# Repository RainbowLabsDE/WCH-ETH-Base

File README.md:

# WCH-ETH-Base
A WCH ETH Board for a Case

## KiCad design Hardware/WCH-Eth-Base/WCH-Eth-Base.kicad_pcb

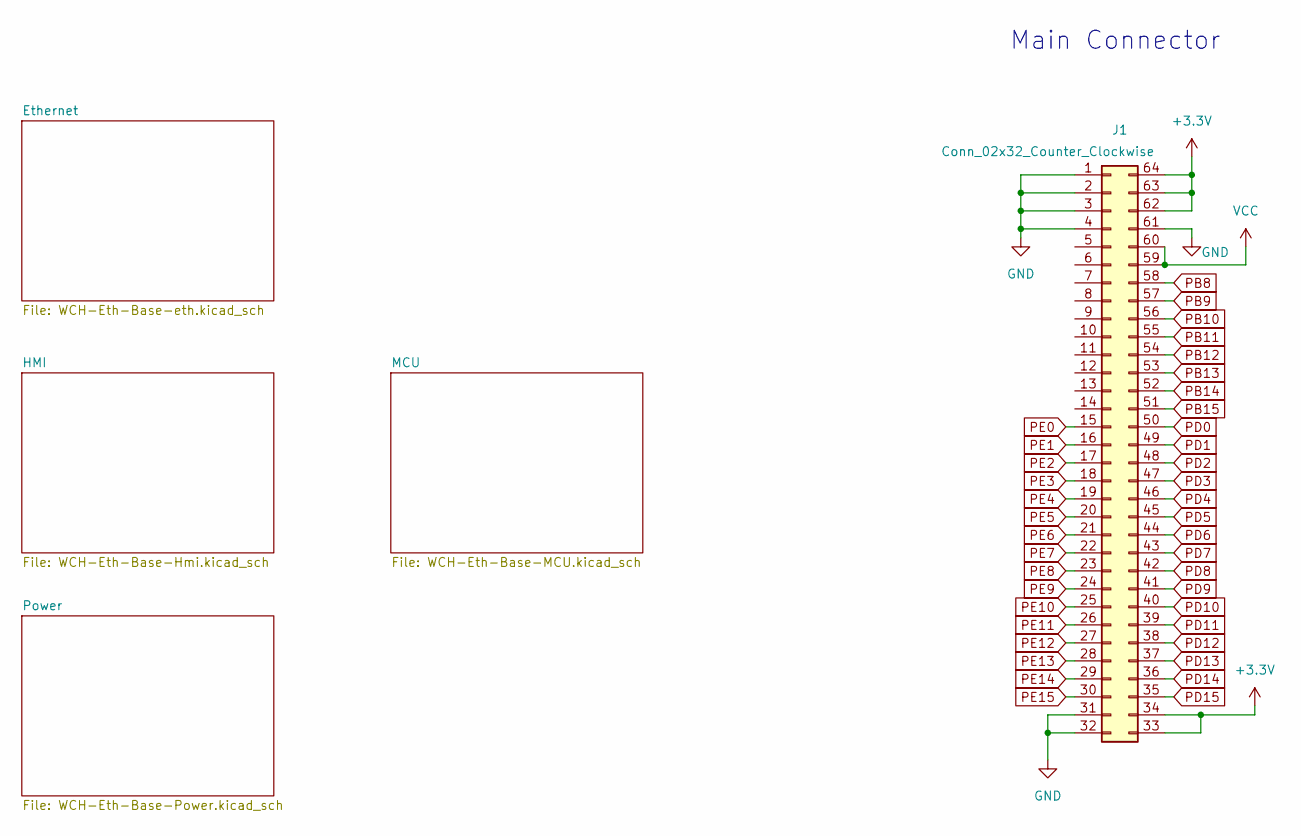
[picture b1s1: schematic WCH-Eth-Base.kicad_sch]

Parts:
J1: Conn_02x32_Counter_Clockwise; CONN-SMD_64P_3157-10101D

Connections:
+3.3V: J1.33, J1.34, J1.62, J1.63, J1.64; also elsewhere on the board
GND: J1.1, J1.2, J1.3, J1.4, J1.31, J1.32, J1.61; also elsewhere on the board
PB8: J1.58; also elsewhere on the board
PB9: J1.57; also elsewhere on the board
PB10: J1.56; also elsewhere on the board
PB11: J1.55; also elsewhere on the board
PB12: J1.54; also elsewhere on the board
PB13: J1.53; also elsewhere on the board
PB14: J1.52; also elsewhere on the board
PB15: J1.51; also elsewhere on the board
PD0: J1.50; also elsewhere on the board
PD1: J1.49; also elsewhere on the board
PD2: J1.48; also elsewhere on the board
PD3: J1.47; also elsewhere on the board
PD4: J1.46; also elsewhere on the board
PD5: J1.45; also elsewhere on the board
PD6: J1.44; also elsewhere on the board
PD7: J1.43; also elsewhere on the board
PD8: J1.42; also elsewhere on the board
PD9: J1.41; also elsewhere on the board
PD10: J1.40; also elsewhere on the board
PD11: J1.39; also elsewhere on the board
PD12: J1.38; also elsewhere on the board
PD13: J1.37; also elsewhere on the board
PD14: J1.36; also elsewhere on the board
PD15: J1.35; also elsewhere on the board
PE0: J1.15; also elsewhere on the board
PE1: J1.16; also elsewhere on the board
PE2: J1.17; also elsewhere on the board
PE3: J1.18; also elsewhere on the board
PE4: J1.19; also elsewhere on the board
PE5: J1.20; also elsewhere on the board
PE6: J1.21; also elsewhere on the board
PE7: J1.22; also elsewhere on the board
PE8: J1.23; also elsewhere on the board
PE9: J1.24; also elsewhere on the board
PE10: J1.25; also elsewhere on the board
PE11: J1.26; also elsewhere on the board
PE12: J1.27; also elsewhere on the board
PE13: J1.28; also elsewhere on the board
PE14: J1.29; also elsewhere on the board
PE15: J1.30; also elsewhere on the board
VCC: J1.59, J1.60; also elsewhere on the board

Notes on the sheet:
Main Connector

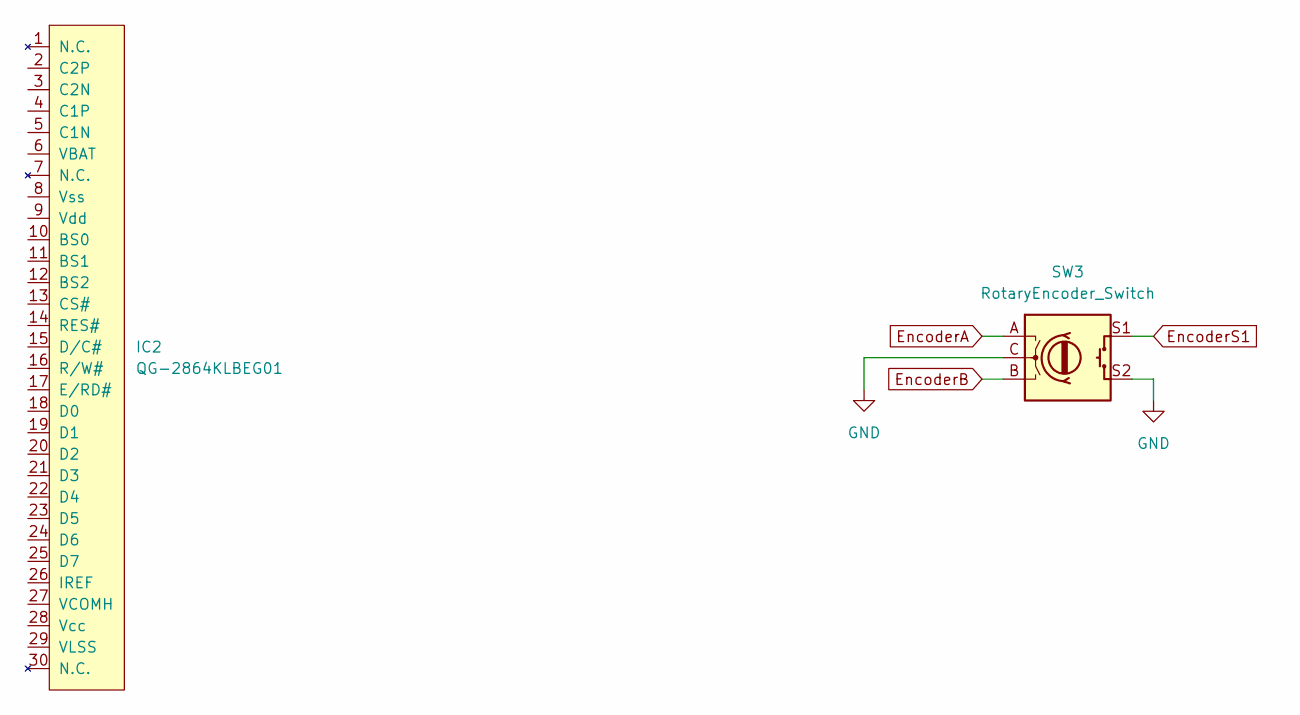
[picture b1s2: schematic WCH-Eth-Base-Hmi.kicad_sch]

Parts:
IC2: QG-2864KLBEG01
SW3: RotaryEncoder_Switch; STEC11B09

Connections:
EncoderA: SW3.A
EncoderB: SW3.B
EncoderS1: SW3.S1
GND: SW3.C, SW3.S2; also elsewhere on the board

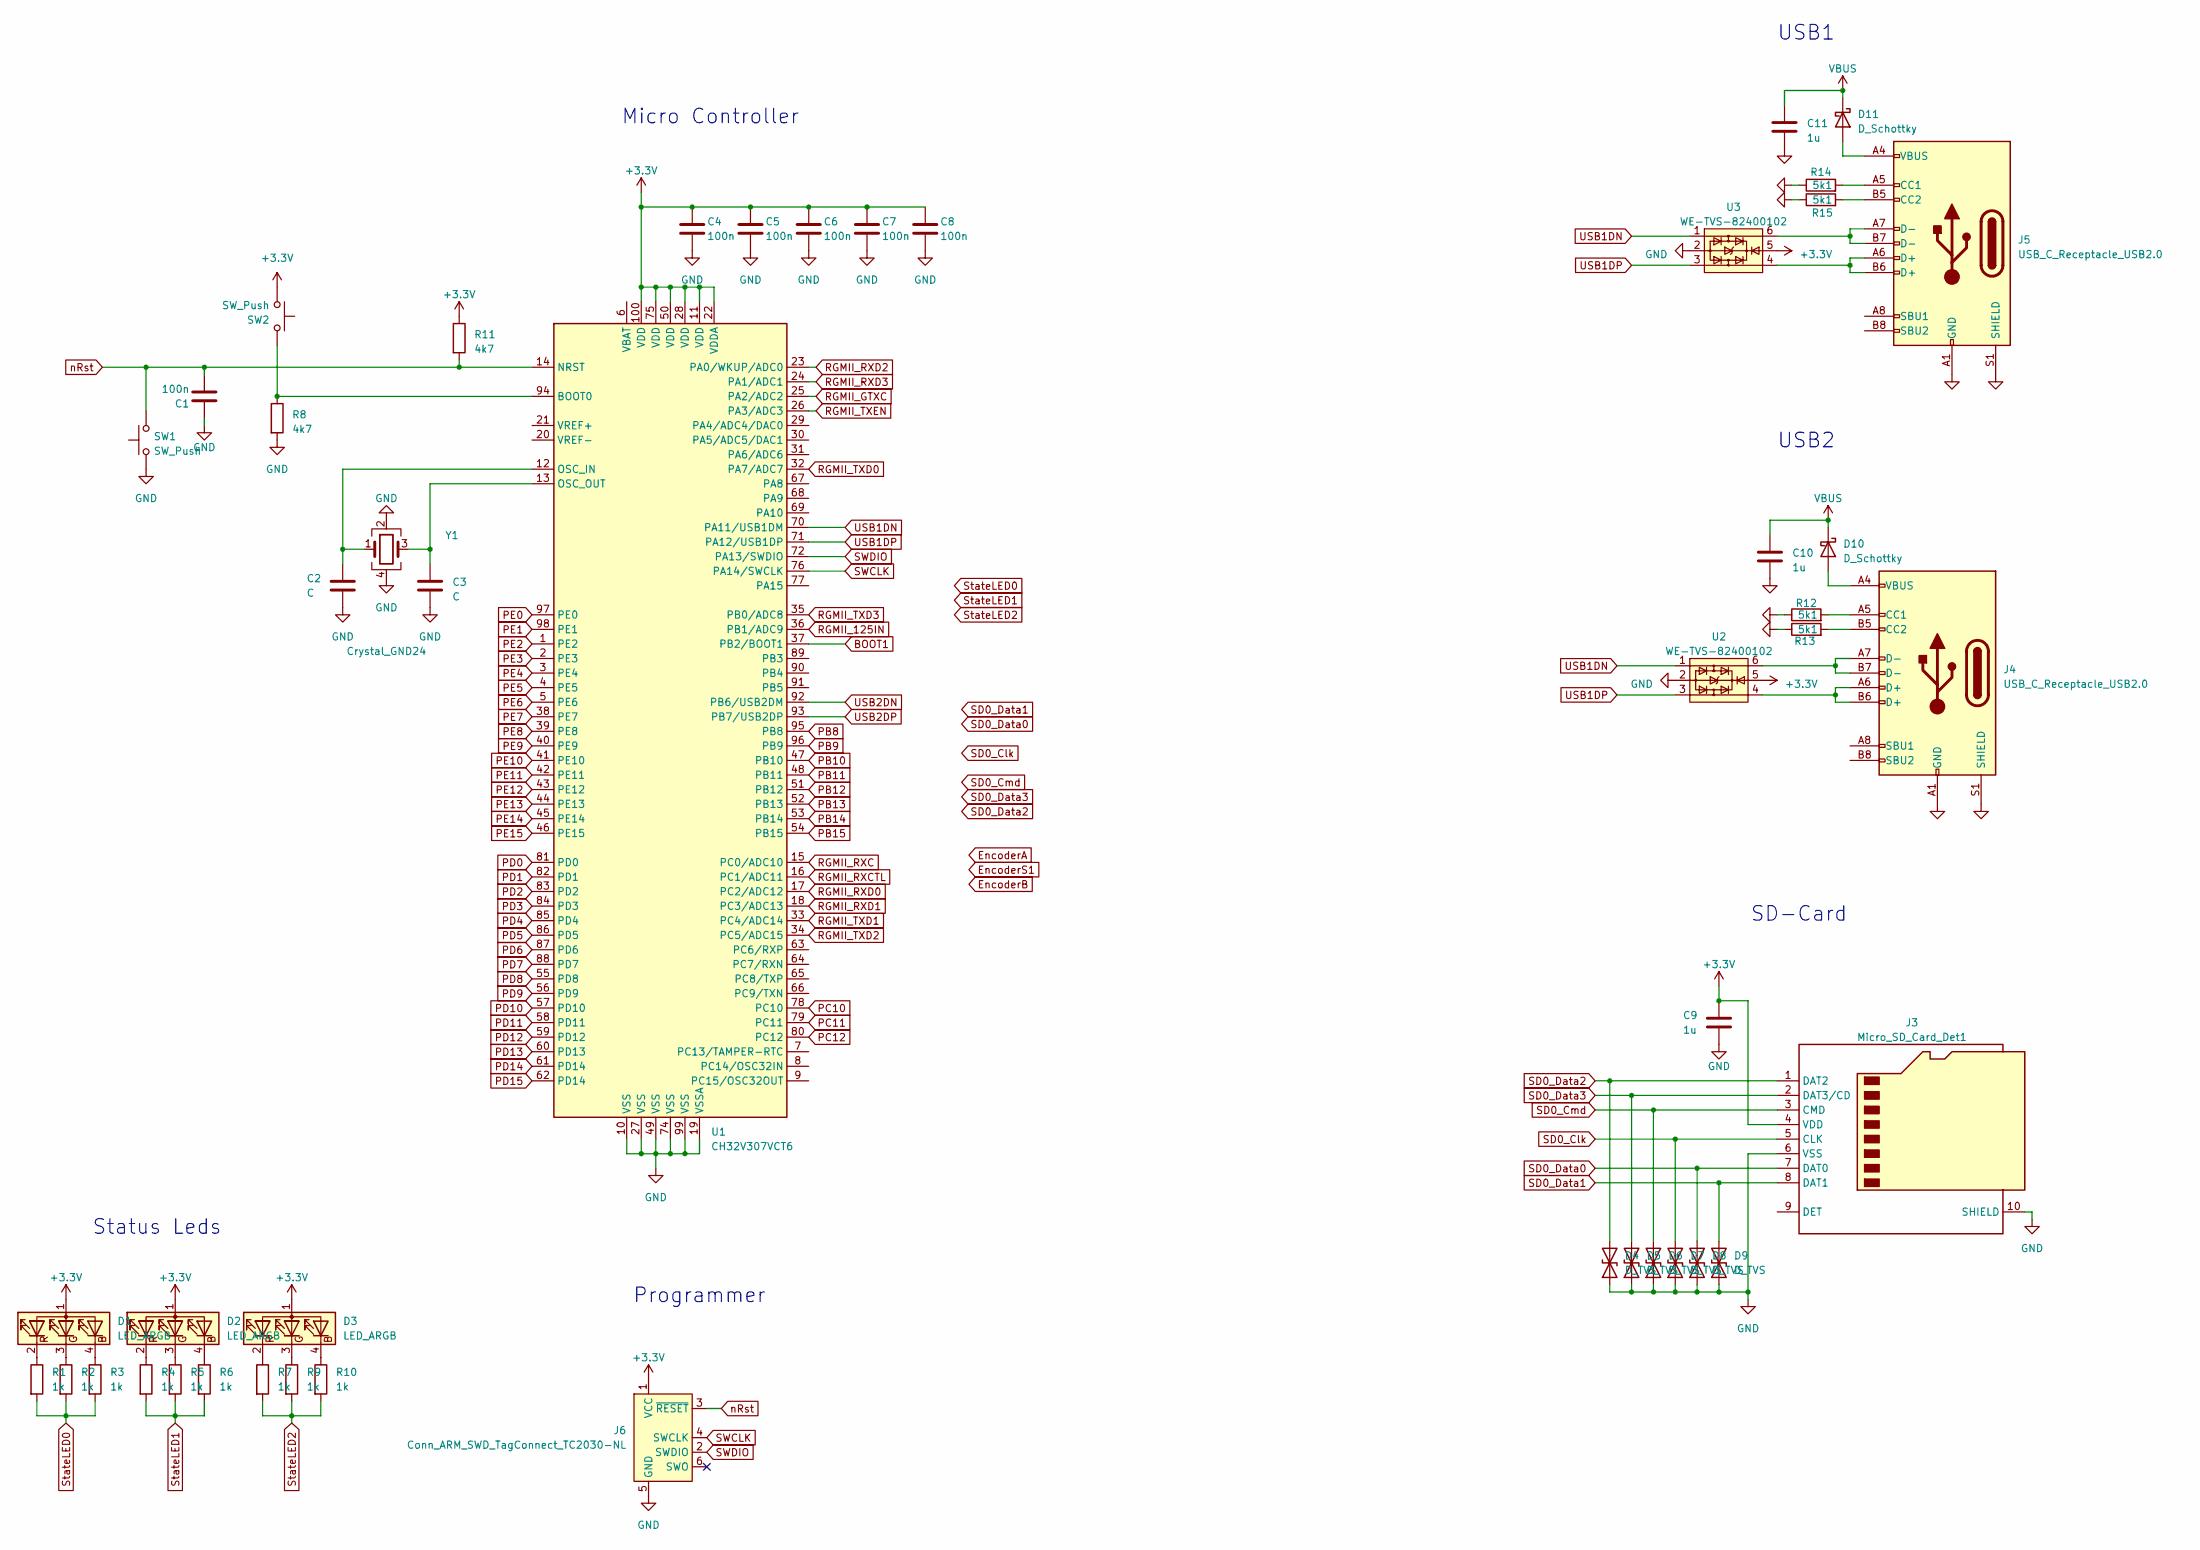
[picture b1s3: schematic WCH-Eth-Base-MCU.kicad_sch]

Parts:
C1, C4, C5, C6, C7, C8: 100n; C_0402_1005Metric
C2, C3: C; C_0402_1005Metric
C9, C10, C11: 1u; C_0402_1005Metric
D1, D2, D3: LED_ARGB; LED-ARRAY-SMD_MHS110FRGBCT
D4: D_TVS; D_SMA
D5, D6, D7, D8, D9: D_TVS
D10, D11: D_Schottky; D_SMA
J3: Micro_SD_Card_Det1
J4, J5: USB_C_Receptacle_USB2.0; TYPE-C-TH_TYPE-C-14P-CC-2.6
J6: Conn_ARM_SWD_TagConnect_TC2030-NL; Tag-Connect_TC2030-IDC-NL_2x03_P1.27mm_Vertical
R1, R2, R3, R4, R5, R6, R7, R9, R10: 1k; R_0402_1005Metric
R8, R11: 4k7; R_0402_1005Metric
R12, R13, R14, R15: 5k1; R_0402_1005Metric
SW1, SW2: SW_Push; SW-SMD_4P-L5.1-W5.1-P3.70-LS6.5-TL-2
U1: CH32V307VCT6; LQFP-100_14x14mm_P0.5mm
U2, U3: WE-TVS-82400102; SOT-23-6
Y1: Crystal_GND24; Crystal_SMD_3225-4Pin_3.2x2.5mm

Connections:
+3.3V: C4.1, C5.1, C6.1, C7.1, C8.1, C9.1, D1.1 (A), D2.1 (A), D3.1 (A), J3.4 (VDD), J6.1 (VCC), R11.1, SW2.1, U1.11 (VDD), U1.22 (VDDA), U1.28 (VDD), U1.50 (VDD), U1.75 (VDD), U1.100 (VDD), U2.5, U3.5; also elsewhere on the board
BOOT1: U1.37 (PB2/BOOT1)
GND: C1.1, C2.2, C3.2, C4.2, C5.2, C6.2, C7.2, C8.2, C9.2, C10.2, C11.2, D4.1 (A1), D5.1 (A1), D6.1 (A1), D7.1 (A1), D8.1 (A1), D9.1 (A1), J3.6 (VSS), J3.10 (SHIELD), J4.A1 (GND), J4.A12 (GND), J4.B1 (GND), J4.B12 (GND), J4.S1 (SHIELD), J5.A1 (GND), J5.A12 (GND), J5.B1 (GND), J5.B12 (GND), J5.S1 (SHIELD), J6.5 (GND), R8.2, R12.1, R13.1, R14.1, R15.1, SW1.1, U1.10 (VSS), U1.19 (VSSA), U1.27 (VSS), U1.49 (VSS), U1.74 (VSS), U1.99 (VSS), U2.2, U3.2, Y1.2, Y1.4; also elsewhere on the board
unnamed: D1.4 (BK), R3.1
unnamed: D1.3 (GK), R2.1
unnamed: D1.2 (RK), R1.1
unnamed: D2.4 (BK), R6.1
unnamed: D2.3 (GK), R5.1
unnamed: D2.2 (RK), R4.1
unnamed: D3.4 (BK), R10.1
unnamed: D3.3 (GK), R9.1
unnamed: D3.2 (RK), R7.1
unnamed: D5.2 (A2), J3.2 (DAT3/CD)
unnamed: D6.2 (A2), J3.3 (CMD)
unnamed: D7.2 (A2), J3.5 (CLK)
unnamed: D8.2 (A2), J3.7 (DAT0)
unnamed: D9.2 (A2), J3.8 (DAT1)
unnamed: D10.2 (A), J4.A4 (VBUS), J4.A9 (VBUS), J4.B4 (VBUS), J4.B9 (VBUS)
unnamed: D11.2 (A), J5.A4 (VBUS), J5.A9 (VBUS), J5.B4 (VBUS), J5.B9 (VBUS)
unnamed: J4.A5 (CC1), R12.2
unnamed: J4.B5 (CC2), R13.2
unnamed: J4.A6 (D+), J4.B6 (D+), U2.4
unnamed: J4.A7 (D-), J4.B7 (D-), U2.6
unnamed: J5.A5 (CC1), R14.2
unnamed: J5.B5 (CC2), R15.2
unnamed: J5.A6 (D+), J5.B6 (D+), U3.4
unnamed: J5.A7 (D-), J5.B7 (D-), U3.6
unnamed: R8.1, SW2.2, U1.94 (BOOT0)
unnamed: C2.1, U1.12 (OSC_IN), Y1.1
unnamed: C3.1, U1.13 (OSC_OUT), Y1.3
PB8: U1.95 (PB8); also elsewhere on the board
PB9: U1.96 (PB9); also elsewhere on the board
PB10: U1.47 (PB10); also elsewhere on the board
PB11: U1.48 (PB11); also elsewhere on the board
PB12: U1.51 (PB12); also elsewhere on the board
PB13: U1.52 (PB13); also elsewhere on the board
PB14: U1.53 (PB14); also elsewhere on the board
PB15: U1.54 (PB15); also elsewhere on the board
PC10: U1.78 (PC10)
PC11: U1.79 (PC11)
PC12: U1.80 (PC12)
PD0: U1.81 (PD0); also elsewhere on the board
PD1: U1.82 (PD1); also elsewhere on the board
PD2: U1.83 (PD2); also elsewhere on the board
PD3: U1.84 (PD3); also elsewhere on the board
PD4: U1.85 (PD4); also elsewhere on the board
PD5: U1.86 (PD5); also elsewhere on the board
PD6: U1.87 (PD6); also elsewhere on the board
PD7: U1.88 (PD7); also elsewhere on the board
PD8: U1.55 (PD8); also elsewhere on the board
PD9: U1.56 (PD9); also elsewhere on the board
PD10: U1.57 (PD10); also elsewhere on the board
PD11: U1.58 (PD11); also elsewhere on the board
PD12: U1.59 (PD12); also elsewhere on the board
PD13: U1.60 (PD13); also elsewhere on the board
PD14: U1.61 (PD14); also elsewhere on the board
PD15: U1.62 (PD14); also elsewhere on the board
PE0: U1.97 (PE0); also elsewhere on the board
PE1: U1.98 (PE1); also elsewhere on the board
PE2: U1.1 (PE2); also elsewhere on the board
PE3: U1.2 (PE3); also elsewhere on the board
PE4: U1.3 (PE4); also elsewhere on the board
PE5: U1.4 (PE5); also elsewhere on the board
PE6: U1.5 (PE6); also elsewhere on the board
PE7: U1.38 (PE7); also elsewhere on the board
PE8: U1.39 (PE8); also elsewhere on the board
PE9: U1.40 (PE9); also elsewhere on the board
PE10: U1.41 (PE10); also elsewhere on the board
PE11: U1.42 (PE11); also elsewhere on the board
PE12: U1.43 (PE12); also elsewhere on the board
PE13: U1.44 (PE13); also elsewhere on the board
PE14: U1.45 (PE14); also elsewhere on the board
PE15: U1.46 (PE15); also elsewhere on the board
RGMII_125IN: U1.36 (PB1/ADC9)
RGMII_GTXC: U1.25 (PA2/ADC2)
RGMII_RXC: U1.15 (PC0/ADC10)
RGMII_RXCTL: U1.16 (PC1/ADC11)
RGMII_RXD0: U1.17 (PC2/ADC12)
RGMII_RXD1: U1.18 (PC3/ADC13)
RGMII_RXD2: U1.23 (PA0/WKUP/ADC0)
RGMII_RXD3: U1.24 (PA1/ADC1)
RGMII_TXD0: U1.32 (PA7/ADC7)
RGMII_TXD1: U1.33 (PC4/ADC14)
RGMII_TXD2: U1.34 (PC5/ADC15)
RGMII_TXD3: U1.35 (PB0/ADC8)
RGMII_TXEN: U1.26 (PA3/ADC3)
SD0_Data2: D4.2 (A2), J3.1 (DAT2)
SWCLK: J6.4 (SWCLK), U1.76 (PA14/SWCLK)
SWDIO: J6.2 (SWDIO), U1.72 (PA13/SWDIO)
StateLED0: R1.2, R2.2, R3.2
StateLED1: R4.2, R5.2, R6.2
StateLED2: R7.2, R9.2, R10.2
USB1DN: U1.70 (PA11/USB1DM), U2.1, U3.1
USB1DP: U1.71 (PA12/USB1DP), U2.3, U3.3
USB2DN: U1.92 (PB6/USB2DM)
USB2DP: U1.93 (PB7/USB2DP)
VBUS: C10.1, C11.1, D10.1 (K), D11.1 (K); also elsewhere on the board
nRst: C1.2, J6.3 (~RESET), R11.2, SW1.2, U1.14 (NRST)

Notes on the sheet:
SD-Card
USB2
Programmer
USB1
Status Leds
Micro Controller

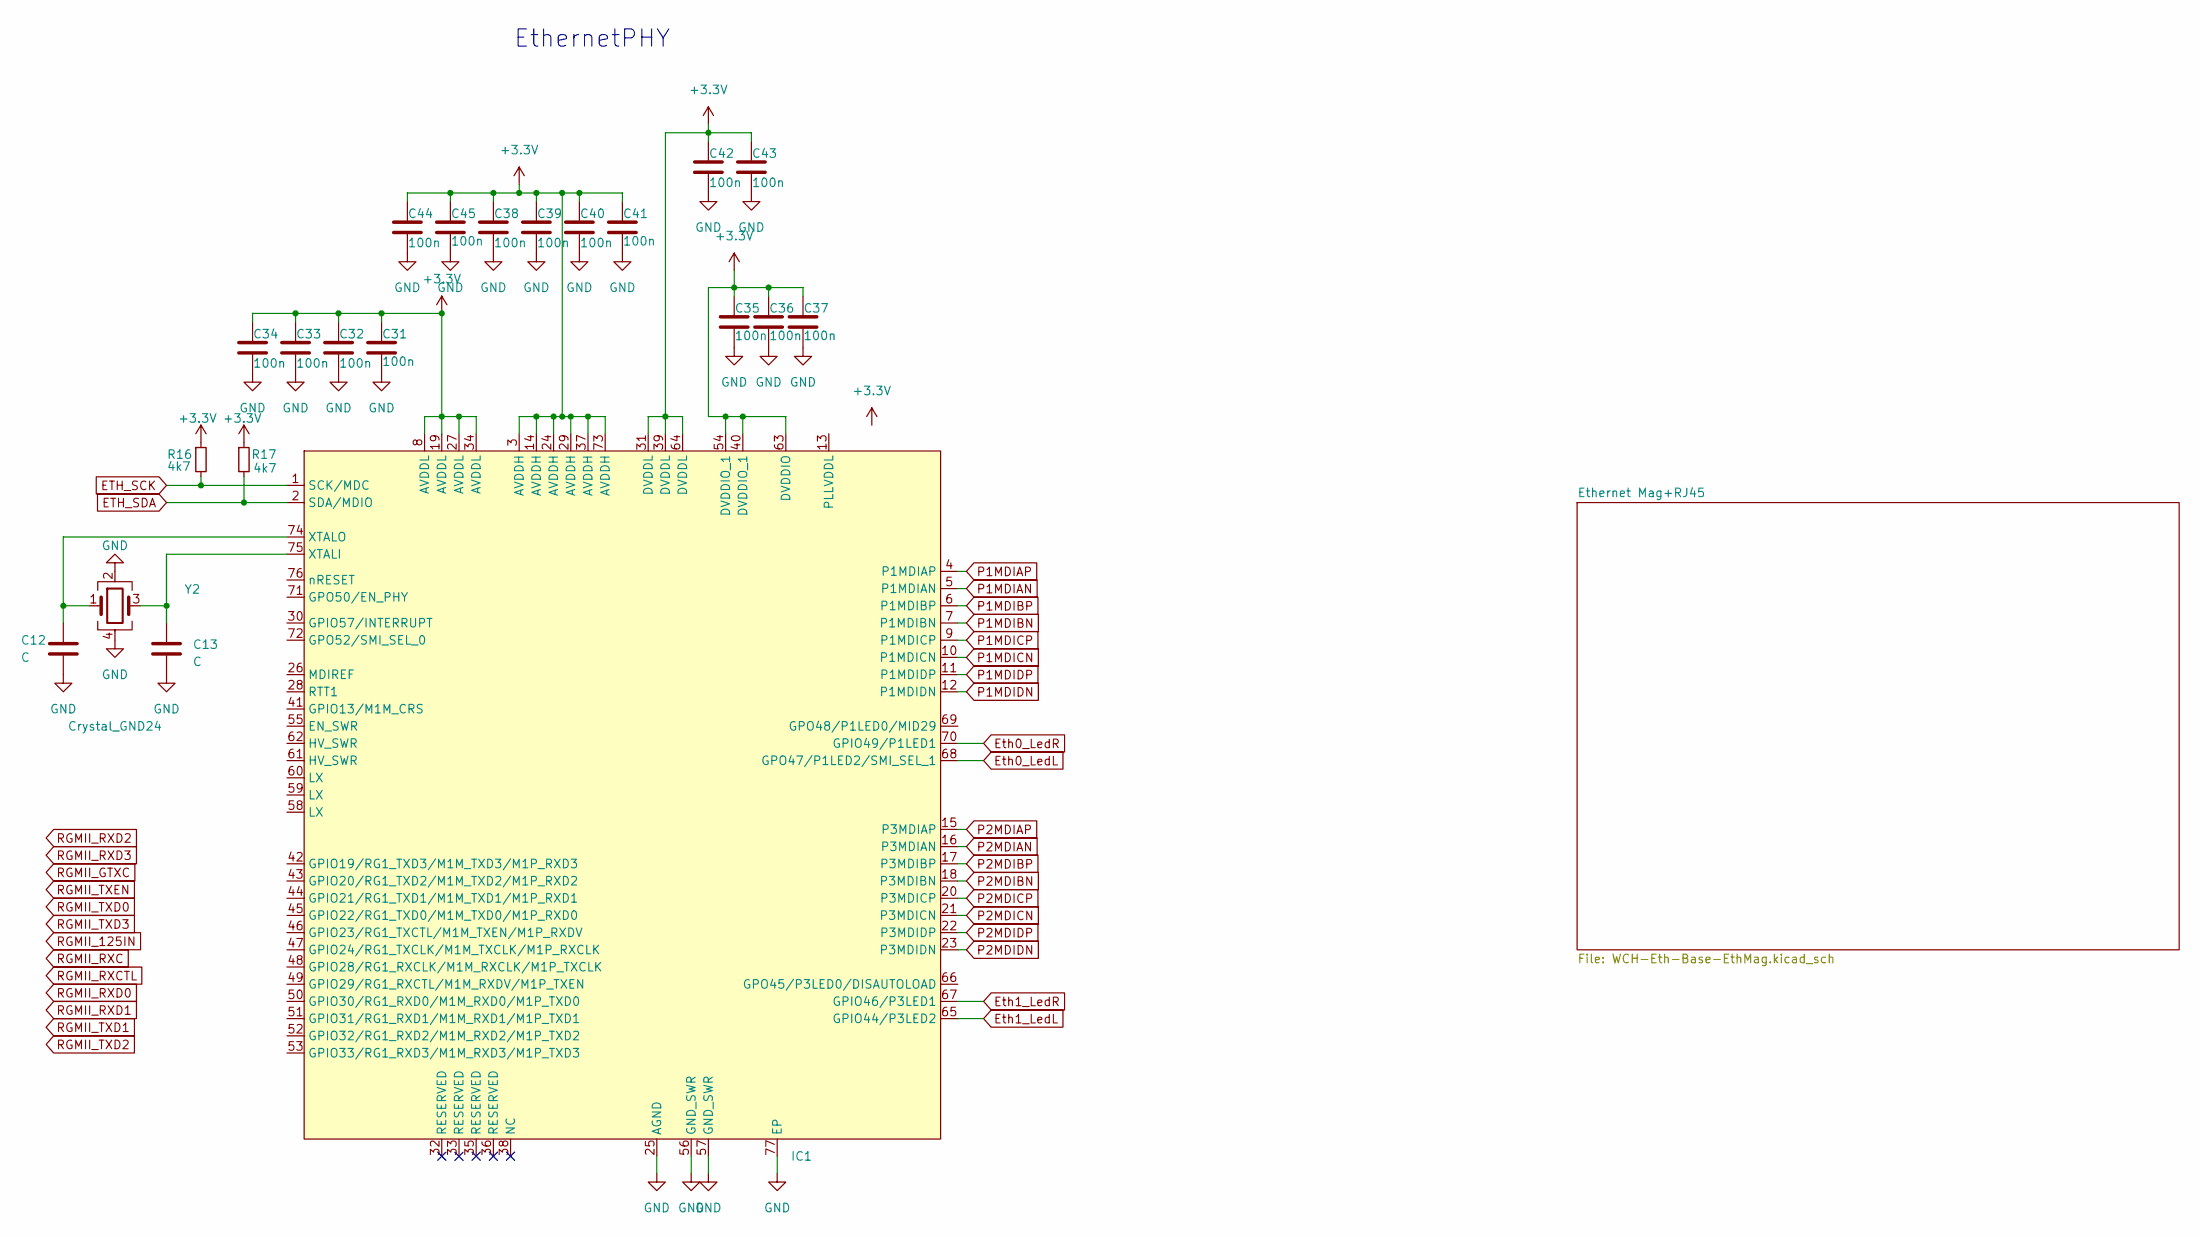
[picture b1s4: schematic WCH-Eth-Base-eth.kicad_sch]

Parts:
C12, C13: C; C_0402_1005Metric
C31, C32, C33, C34, C35, C36, C37, C38, C39, C40, C41, C42, C43, C44, C45: 100n; C_0402_1005Metric
IC1: QFN-76-1EP_9x9mm_P0.4mm_EP5.81x6.31mm
R16, R17: 4k7; R_0402_1005Metric
Y2: Crystal_GND24; Crystal_SMD_3225-4Pin_3.2x2.5mm

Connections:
+3.3V: C31.1, C32.1, C33.1, C34.1, C35.1, C36.1, C37.1, C38.1, C39.1, C40.1, C41.1, C42.1, C43.1, C44.1, C45.1, IC1.3 (AVDDH), IC1.8 (AVDDL), IC1.14 (AVDDH), IC1.19 (AVDDL), IC1.24 (AVDDH), IC1.27 (AVDDL), IC1.29 (AVDDH), IC1.31 (DVDDL), IC1.34 (AVDDL), IC1.37 (AVDDH), IC1.39 (DVDDL), IC1.40 (DVDDIO_1), IC1.54 (DVDDIO_1), IC1.63 (DVDDIO), IC1.64 (DVDDL), IC1.73 (AVDDH), R16.1, R17.1; also elsewhere on the board
ETH_SCK: IC1.1 (SCK/MDC), R16.2
ETH_SDA: IC1.2 (SDA/MDIO), R17.2
Eth0_LedL: IC1.68 (GPO47/P1LED2/SMI_SEL_1); also elsewhere on the board
Eth0_LedR: IC1.70 (GPIO49/P1LED1); also elsewhere on the board
Eth1_LedL: IC1.65 (GPIO44/P3LED2); also elsewhere on the board
Eth1_LedR: IC1.67 (GPIO46/P3LED1); also elsewhere on the board
GND: C12.2, C13.2, C31.2, C32.2, C33.2, C34.2, C35.2, C36.2, C37.2, C38.2, C39.2, C40.2, C41.2, C42.2, C43.2, C44.2, C45.2, IC1.25 (AGND), IC1.56 (GND_SWR), IC1.57 (GND_SWR), IC1.77 (EP), Y2.2, Y2.4; also elsewhere on the board
unnamed: C13.1, IC1.75 (XTALI), Y2.3
unnamed: C12.1, IC1.74 (XTALO), Y2.1
P1MDIAN: IC1.5 (P1MDIAN); also elsewhere on the board
P1MDIAP: IC1.4 (P1MDIAP); also elsewhere on the board
P1MDIBN: IC1.7 (P1MDIBN); also elsewhere on the board
P1MDIBP: IC1.6 (P1MDIBP); also elsewhere on the board
P1MDICN: IC1.10 (P1MDICN); also elsewhere on the board
P1MDICP: IC1.9 (P1MDICP); also elsewhere on the board
P1MDIDN: IC1.12 (P1MDIDN); also elsewhere on the board
P1MDIDP: IC1.11 (P1MDIDP); also elsewhere on the board
P2MDIAN: IC1.16 (P3MDIAN); also elsewhere on the board
P2MDIAP: IC1.15 (P3MDIAP); also elsewhere on the board
P2MDIBN: IC1.18 (P3MDIBN); also elsewhere on the board
P2MDIBP: IC1.17 (P3MDIBP); also elsewhere on the board
P2MDICN: IC1.21 (P3MDICN); also elsewhere on the board
P2MDICP: IC1.20 (P3MDICP); also elsewhere on the board
P2MDIDN: IC1.23 (P3MDIDN); also elsewhere on the board
P2MDIDP: IC1.22 (P3MDIDP); also elsewhere on the board

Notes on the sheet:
EthernetPHY

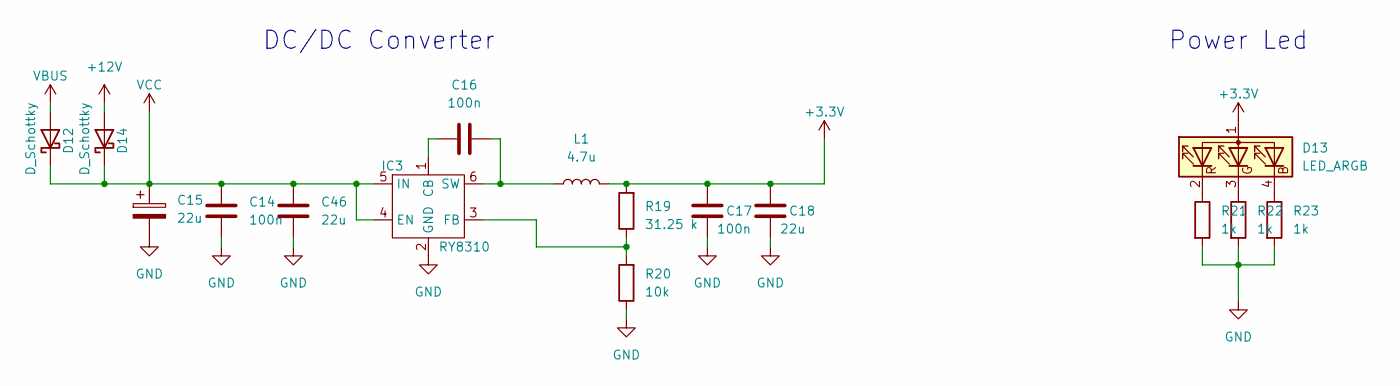
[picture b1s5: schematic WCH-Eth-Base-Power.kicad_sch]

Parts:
C14, C16, C17: 100n; C_0402_1005Metric
C15: 22u; CP_Elec_5x5.4
C18, C46: 22u; C_0402_1005Metric
D12, D14: D_Schottky; D_SMA
D13: LED_ARGB; LED-ARRAY-SMD_MHS110FRGBCT
IC3: RY8310; SOT-23-6
L1: 4.7u; L_0630
R19: 31.25 k; R_0402_1005Metric
R20: 10k; R_0402_1005Metric
R21, R22, R23: 1k; R_0402_1005Metric

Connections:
+3.3V: C17.1, C18.1, D13.1 (A), L1.2, R19.2; also elsewhere on the board
+12V: D14.2 (A); also elsewhere on the board
GND: C14.2, C15.2, C17.2, C18.2, C46.2, IC3.2 (GND), R20.1, R21.2, R22.2, R23.2; also elsewhere on the board
unnamed: D13.4 (BK), R23.1
unnamed: D13.3 (GK), R22.1
unnamed: D13.2 (RK), R21.1
unnamed: C16.1, IC3.1 (CB)
unnamed: IC3.3 (FB), R19.1, R20.2
unnamed: C16.2, IC3.6 (SW), L1.1
VBUS: D12.2 (A); also elsewhere on the board
VCC: C14.1, C15.1, C46.1, D12.1 (K), D14.1 (K), IC3.4 (EN), IC3.5 (IN); also elsewhere on the board

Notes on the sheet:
Power Led
DC/DC Converter

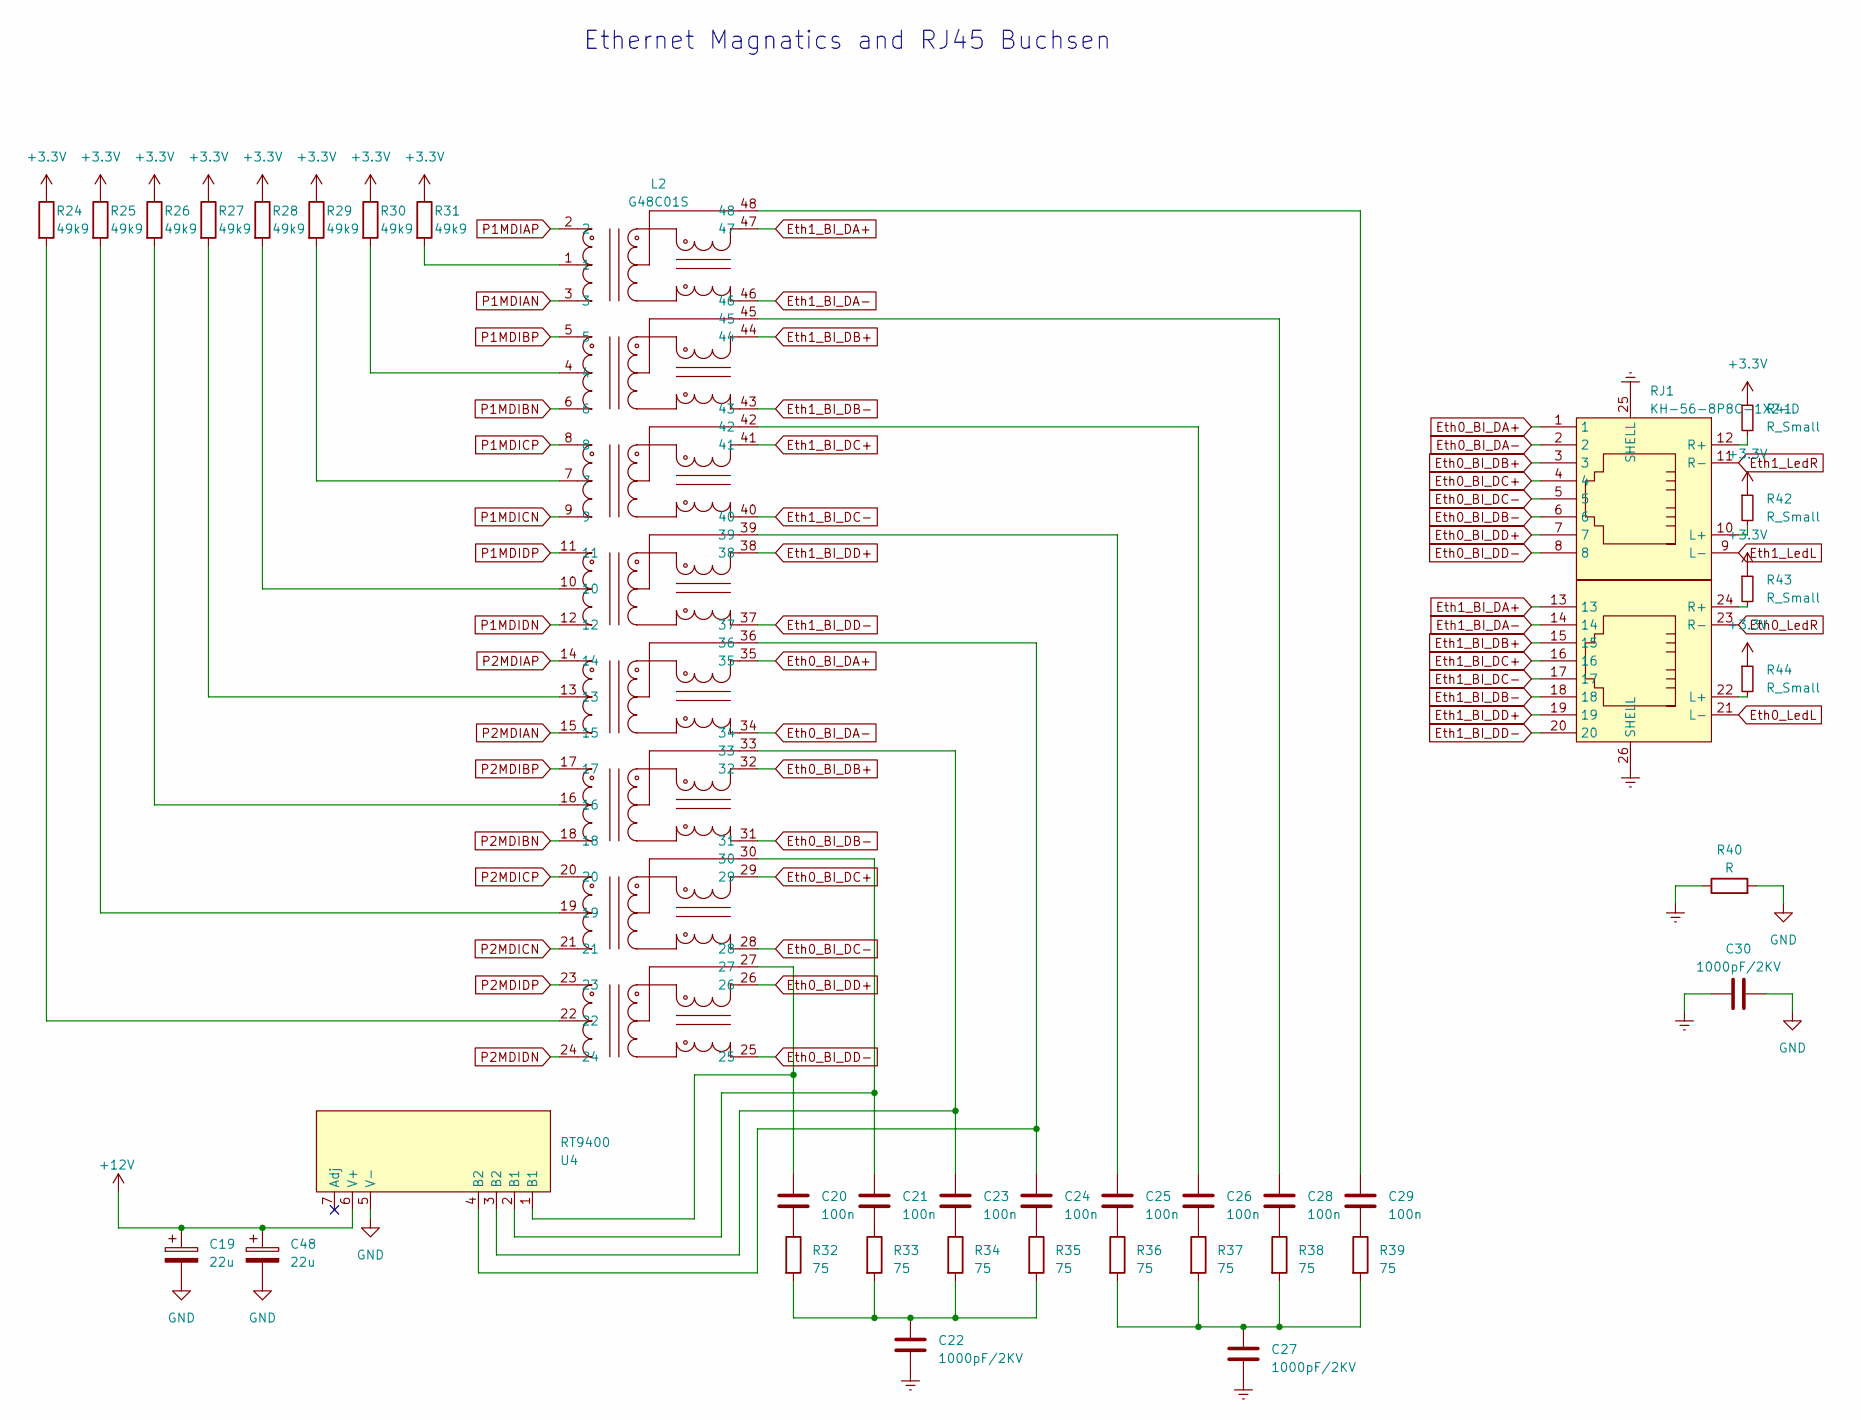
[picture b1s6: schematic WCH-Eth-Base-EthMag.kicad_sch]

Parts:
C19, C48: 22u; CP_Elec_5x5.4
C20, C21, C23, C24, C25, C26, C28, C29: 100n; C_0402_1005Metric
C22, C27, C30: 1000pF/2KV; C_1206_3216Metric
L2: G48C01S; SMD-48_L27.8-W12.3-P1.02-LS15.3-BL; LCSC Part C2827284
R24, R25, R26, R27, R28, R29, R30, R31: 49k9; R_0402_1005Metric
R32, R33, R34, R35, R36, R37, R38, R39: 75; R_0402_1005Metric
R40: R; C_1206_3216Metric
R41, R42, R43, R44: R_Small; R_0402_1005Metric
RJ1: KH-56-8P8C-1X2-D; RJ45-TH_KH-56-8P8C-1X2-D; LCSC Part C2828088
U4: RT9400

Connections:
+3.3V: R24.1, R25.1, R26.1, R27.1, R28.1, R29.1, R30.1, R31.1, R41.1, R42.1, R43.1, R44.1; also elsewhere on the board
+12V: C19.1, C48.1, U4.6 (V+); also elsewhere on the board
Earth: C22.2, C27.2, C30.1, R40.1, RJ1.25 (SHELL), RJ1.26 (SHELL)
Eth0_BI_DA+: L2.35, RJ1.1
Eth0_BI_DA-: L2.34, RJ1.2
Eth0_BI_DB+: L2.32, RJ1.3
Eth0_BI_DB-: L2.31, RJ1.6
Eth0_BI_DC+: L2.29, RJ1.4
Eth0_BI_DC-: L2.28, RJ1.5
Eth0_BI_DD+: L2.26, RJ1.7
Eth0_BI_DD-: L2.25, RJ1.8
Eth0_LedL: RJ1.21 (L-); also elsewhere on the board
Eth0_LedR: RJ1.23 (R-); also elsewhere on the board
Eth1_BI_DA+: L2.47, RJ1.13
Eth1_BI_DA-: L2.46, RJ1.14
Eth1_BI_DB+: L2.44, RJ1.15
Eth1_BI_DB-: L2.43, RJ1.18
Eth1_BI_DC+: L2.41, RJ1.16
Eth1_BI_DC-: L2.40, RJ1.17
Eth1_BI_DD+: L2.38, RJ1.19
Eth1_BI_DD-: L2.37, RJ1.20
Eth1_LedL: RJ1.9 (L-); also elsewhere on the board
Eth1_LedR: RJ1.11 (R-); also elsewhere on the board
GND: C19.2, C30.2, C48.2, R40.2, U4.5 (V-); also elsewhere on the board
unnamed: C20.1, L2.27, U4.1 (B1)
unnamed: C20.2, R32.1
unnamed: C21.1, L2.30, U4.2 (B1)
unnamed: C21.2, R33.1
unnamed: C22.1, R32.2, R33.2, R34.2, R35.2
unnamed: C23.1, L2.33, U4.3 (B2)
unnamed: C23.2, R34.1
unnamed: C24.1, L2.36, U4.4 (B2)
unnamed: C24.2, R35.1
unnamed: C25.1, L2.39
unnamed: C25.2, R36.1
unnamed: C26.1, L2.42
unnamed: C26.2, R37.1
unnamed: C27.1, R36.2, R37.2, R38.2, R39.2
unnamed: C28.1, L2.45
unnamed: C28.2, R38.1
unnamed: C29.1, L2.48
unnamed: C29.2, R39.1
unnamed: L2.1, R31.2
unnamed: L2.4, R30.2
unnamed: L2.7, R29.2
unnamed: L2.10, R28.2
unnamed: L2.13, R27.2
unnamed: L2.16, R26.2
unnamed: L2.19, R25.2
unnamed: L2.22, R24.2
unnamed: R41.2, RJ1.12 (R+)
unnamed: R42.2, RJ1.10 (L+)
unnamed: R43.2, RJ1.24 (R+)
unnamed: R44.2, RJ1.22 (L+)
P1MDIAN: L2.3; also elsewhere on the board
P1MDIAP: L2.2; also elsewhere on the board
P1MDIBN: L2.6; also elsewhere on the board
P1MDIBP: L2.5; also elsewhere on the board
P1MDICN: L2.9; also elsewhere on the board
P1MDICP: L2.8; also elsewhere on the board
P1MDIDN: L2.12; also elsewhere on the board
P1MDIDP: L2.11; also elsewhere on the board
P2MDIAN: L2.15; also elsewhere on the board
P2MDIAP: L2.14; also elsewhere on the board
P2MDIBN: L2.18; also elsewhere on the board
P2MDIBP: L2.17; also elsewhere on the board
P2MDICN: L2.21; also elsewhere on the board
P2MDICP: L2.20; also elsewhere on the board
P2MDIDN: L2.24; also elsewhere on the board
P2MDIDP: L2.23; also elsewhere on the board

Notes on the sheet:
Ethernet Magnatics and RJ45 Buchsen

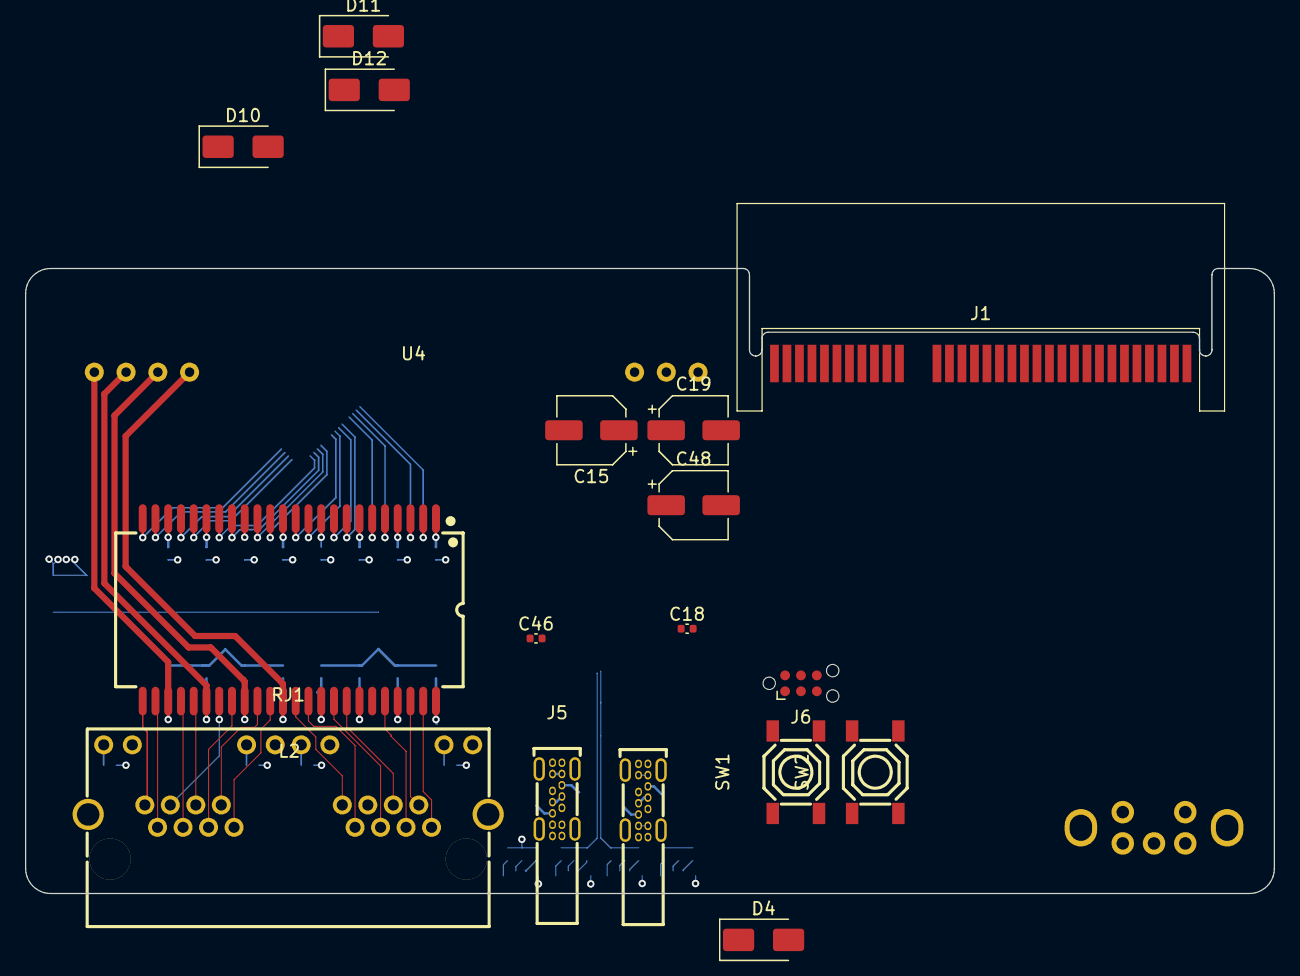
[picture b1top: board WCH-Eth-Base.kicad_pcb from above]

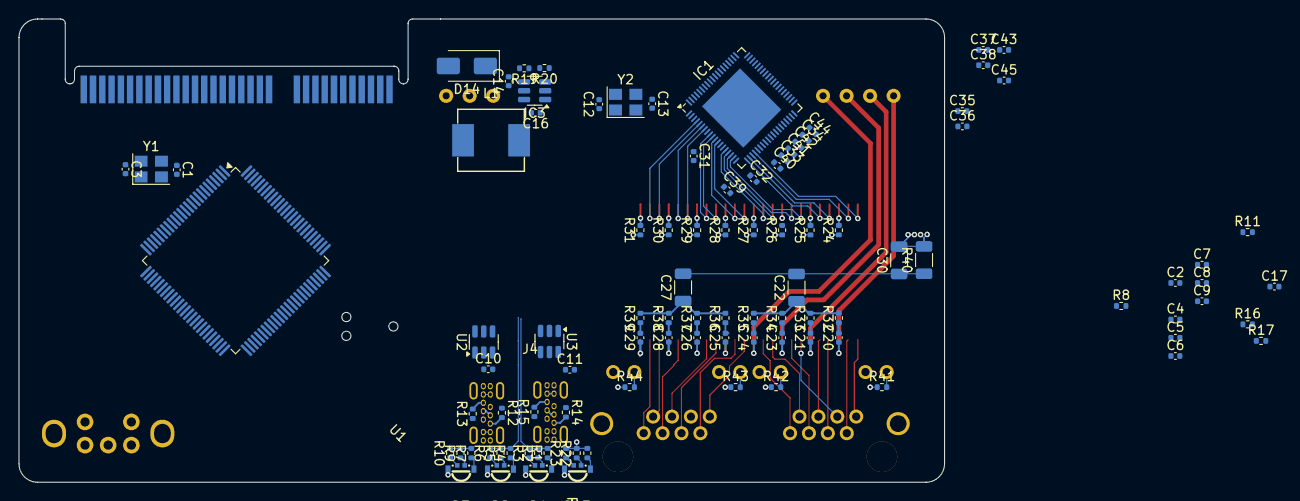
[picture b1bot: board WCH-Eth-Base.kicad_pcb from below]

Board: 4 copper layers, 99.9 x 50.0 mm, 117 parts (98 on the bottom side), 152 nets.

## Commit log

2024-03-22 first push
2024-11-22 add Files and First Layout things
